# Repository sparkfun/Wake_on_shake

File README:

Design files for the Wake-on-shake board.

Firmware compiled in WinAVR-20100110.
EAGLE development in 6.3.0.

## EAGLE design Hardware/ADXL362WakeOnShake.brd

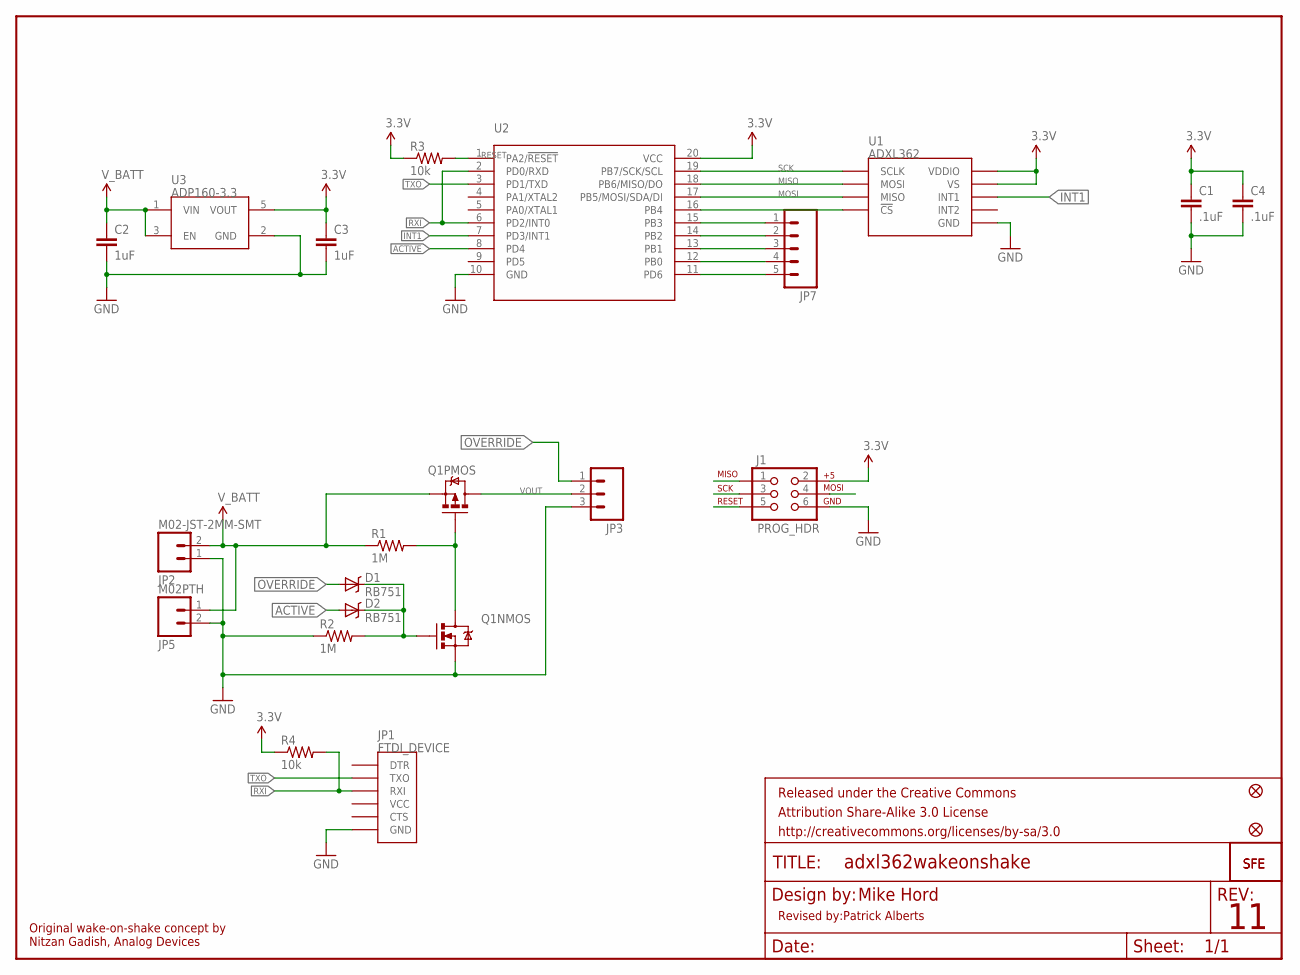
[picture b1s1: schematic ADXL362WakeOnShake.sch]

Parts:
C1, C4: .1uF; 0603-CAP
C2, C3: 1uF; 0603-CAP
D1, D2: RB751; SOD-523
FID1, FID2: FIDUCIAL1X2; FIDUCIAL-1X2
FRAME1: FRAME-LETTER; CREATIVE_COMMONS
J1: PROG_HDR; 2X3
JP1: FTDI_DEVICE; FTDI_DEVICE_SIDE
JP2: M02-JST-2MM-SMT; JST-2-SMD
JP3: M03PTH; 1X03
JP4: LOGO-SFENW2; SFE-NEW-WEB
JP5: M02PTH; 1X02
JP6: LOGO-SFENEW; SFE-NEW-WEBLOGO
JP7: M05PTH; 1X05
Q1: IRF7509; MSOP8
R1, R2: 1M; 0603-RES
R3, R4: 10k; 0603-RES
U1: ADXL362; ADXL362-1:1
U2: ATTINY2313A; SOP20W
U3: ADP160-3.3; SOT23-5

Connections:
3.3V: C1.1, C3.1, C4.1, J1.2, R3.1, R4.1, U1.P$1 (VDDIO), U1.P$14 (VS), U2.20 (VCC), U3.5 (VOUT)
ACTIVE: D2.A, U2.8 (PD4)
GND: C1.2, C2.2, C3.2, C4.2, J1.6, JP1.P$6 (GND), JP2.1 (2), JP3.3, JP5.2, Q1.1 (S), R2.1, U1.P$12 (GND), U1.P$13 (GND), U1.P$16 (GND), U2.10 (GND), U3.2 (GND)
INT1: U1.P$11 (INT1), U2.7 (PD3/INT1)
MISO: J1.1, U1.P$6 (MOSI), U2.18 (PB6/MISO/DO)
MOSI: J1.4, U1.P$7 (MISO), U2.17 (PB5/MOSI/SDA/DI)
unnamed: Q1.4 (G), Q1.7 (D), Q1.8 (D), R1.2
unnamed: D1.C, D2.C, Q1.2 (G), R2.2
unnamed: JP7.1, U2.15 (PB3)
unnamed: JP7.2, U2.14 (PB2)
unnamed: JP7.3, U2.13 (PB1)
unnamed: JP7.4, U2.12 (PB0)
unnamed: U1.P$8 (!CS), U2.16 (PB4)
unnamed: JP7.5, U2.11 (PD6)
OVERRIDE: D1.A, JP3.1
RESET: J1.5, R3.2, U2.1 (PA2/!RESET)
RXI: JP1.P$3 (RXI), R4.2, U2.2 (PD0/RXD), U2.6 (PD2/INT0)
SCK: J1.3, U1.P$4 (SCLK), U2.19 (PB7/SCK/SCL)
TXO: JP1.P$2 (TXO), U2.3 (PD1/TXD)
VOUT: JP3.2, Q1.5 (D), Q1.6 (D)
V_BATT: C2.1, JP2.2 (1), JP5.1, Q1.3 (S), R1.1, U3.1 (VIN), U3.3 (EN)

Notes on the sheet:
Mike Hord
Original wake-on-shake concept by Nitzan Gadish, Analog Devices
Revised by:Patrick Alberts

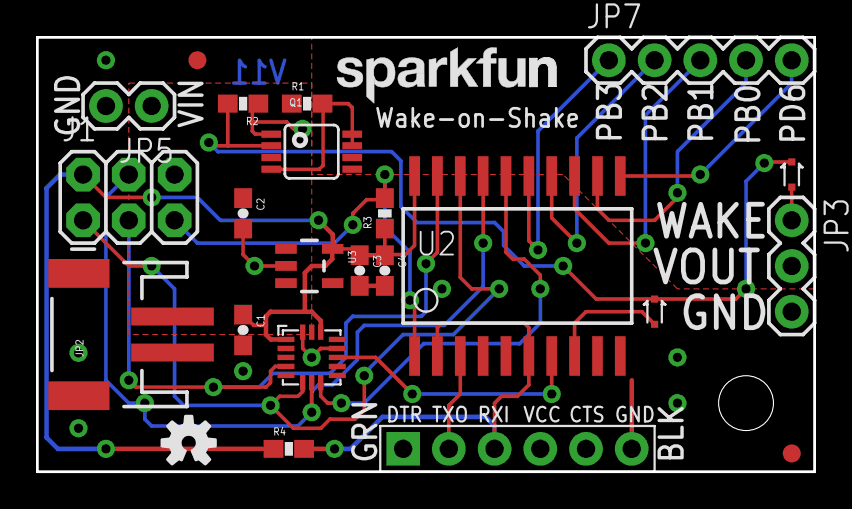
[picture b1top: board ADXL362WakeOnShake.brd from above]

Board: 2 copper layers, 43.2 x 24.1 mm, 27 parts (1 on the bottom side), 21 nets.

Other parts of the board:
U$3: OSHW-LOGO-S
U$4: STAND-OFF-TIGHT

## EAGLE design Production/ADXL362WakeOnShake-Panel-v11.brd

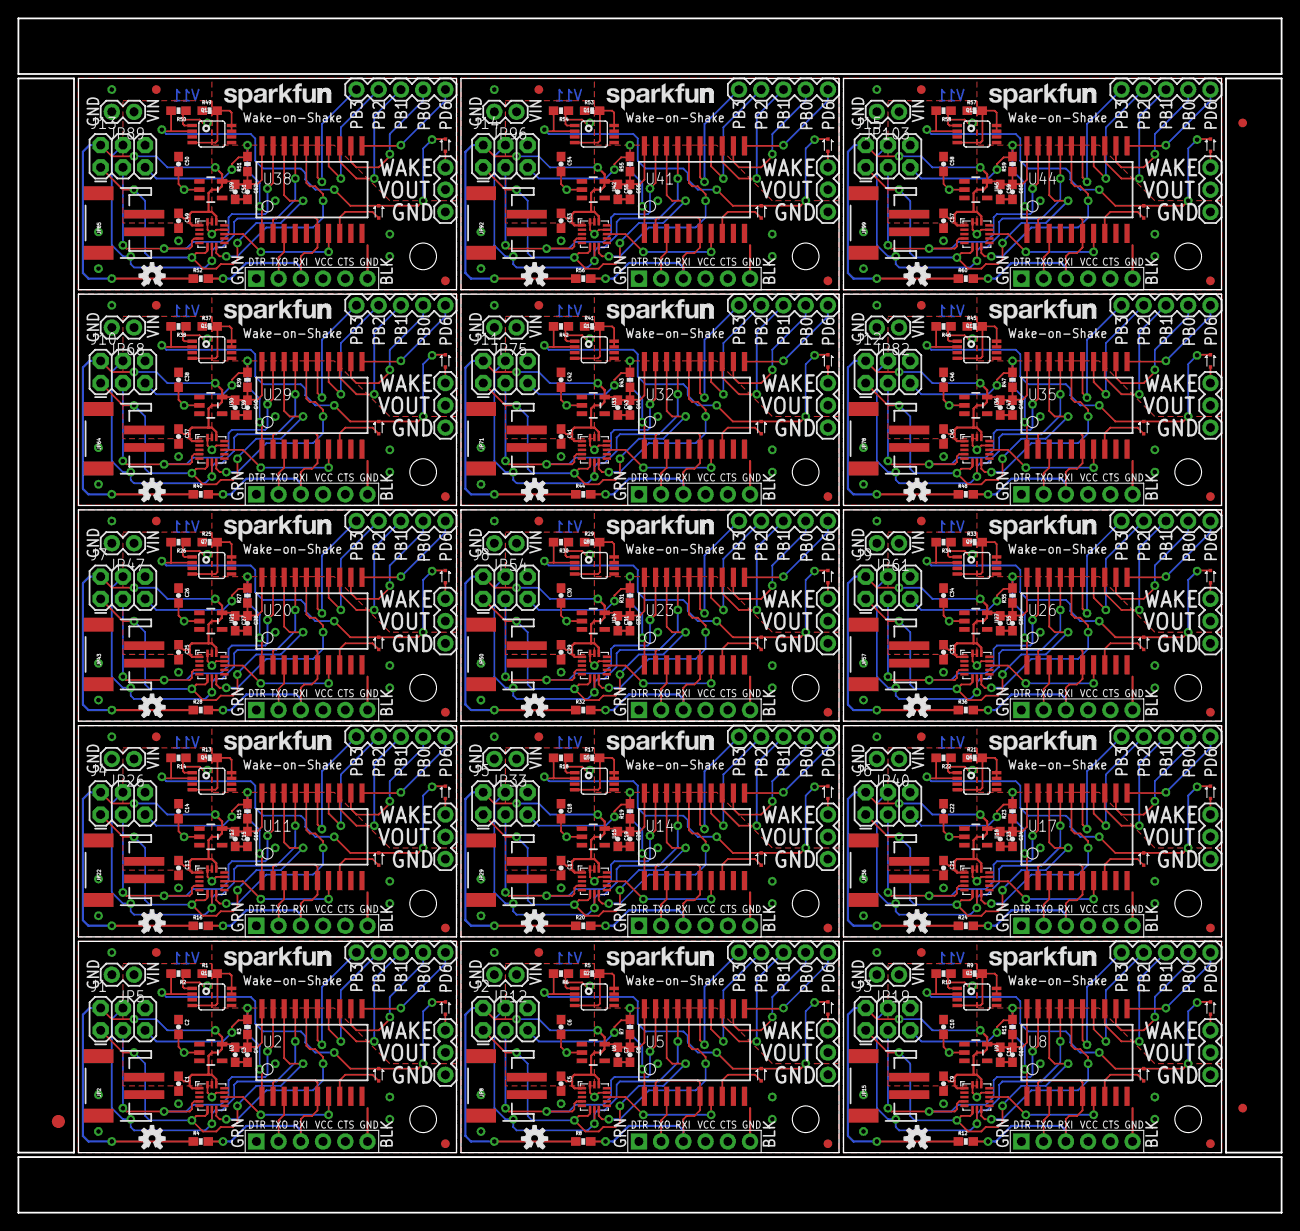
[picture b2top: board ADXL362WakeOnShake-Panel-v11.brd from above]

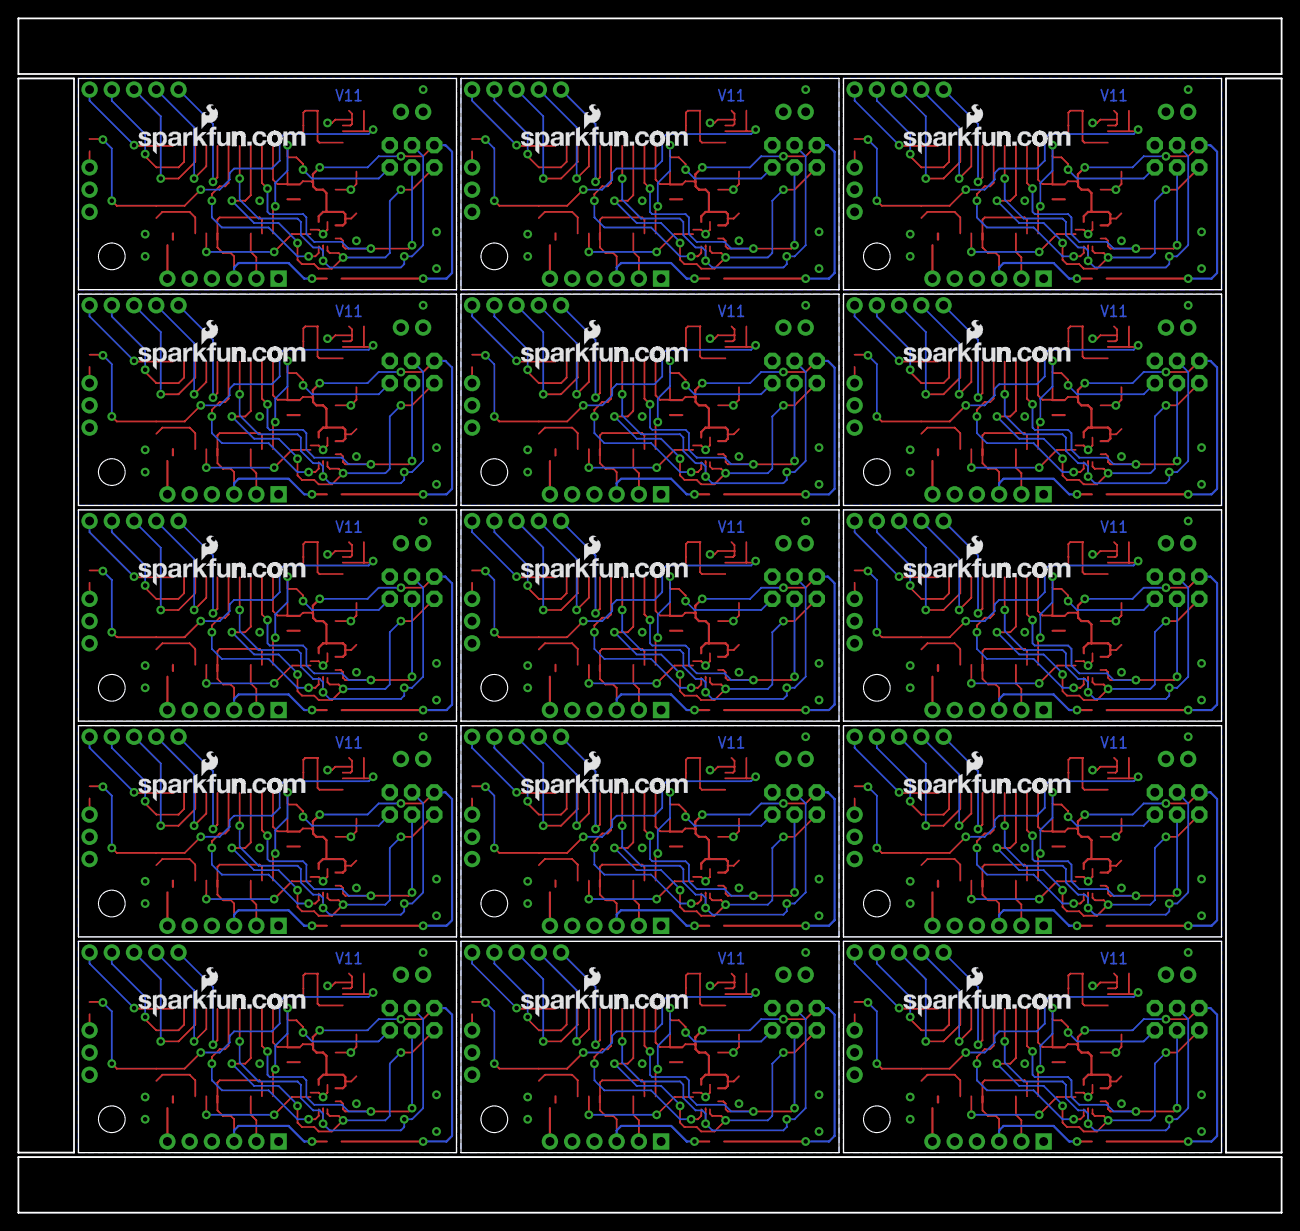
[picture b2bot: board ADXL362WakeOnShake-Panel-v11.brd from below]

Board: 2 copper layers, 144.3 x 136.4 mm, 393 parts (15 on the bottom side), 315 nets.

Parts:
C1, C4, C5, C8, C9, C12, C13, C16, C17, C20, C21, C24, C25, C28, C29, C32, C33, C36, C37, C40, C41, C44, C45, C48, C49, C52, C53, C56, C57, C60: .1uF; 0603-CAP
C2, C3, C6, C7, C10, C11, C14, C15, C18, C19, C22, C23, C26, C27, C30, C31, C34, C35, C38, C39, C42, C43, C46, C47, C50, C51, C54, C55, C58, C59: 1uF; 0603-CAP
D1, D2, D3, D4, D5, D6, D7, D8, D9, D10, D11, D12, D13, D14, D15, D16, D17, D18, D19, D20, D21, D22, D23, D24, D25, D26, D27, D28, D29, D30: RB751; SOD-523
E$1: FIDUCIAL-1.5X3
E$4, E$5: FIDUCIAL-1X2
FID1, FID2, FID3, FID4, FID5, FID6, FID7, FID8, FID9, FID10, FID11, FID12, FID13, FID14, FID15, FID16, FID17, FID18, FID19, FID20, FID21, FID22, FID23, FID24, FID25, FID26, FID27, FID28, FID29, FID30: FIDUCIAL1X2; FIDUCIAL-1X2
J1, J2, J3, J4, J5, J6, J7, J8, J9, J10, J11, J12, J13, J14, J15: PROG_HDR; 2X3
JP1, JP10, JP17, JP24, JP31, JP38, JP45, JP52, JP59, JP66, JP73, JP80, JP87, JP94, JP101: FTDI_DEVICE; FTDI_DEVICE_SIDE
JP2, JP8, JP15, JP22, JP29, JP36, JP43, JP50, JP57, JP64, JP71, JP78, JP85, JP92, JP99: M02-JST-2MM-SMT; JST-2-SMD
JP3, JP9, JP16, JP23, JP30, JP37, JP44, JP51, JP58, JP65, JP72, JP79, JP86, JP93, JP100: 1X03
JP4, JP11, JP18, JP25, JP32, JP39, JP46, JP53, JP60, JP67, JP74, JP81, JP88, JP95, JP102: LOGO-SFENW2; SFE-NEW-WEB
JP5, JP12, JP19, JP26, JP33, JP40, JP47, JP54, JP61, JP68, JP75, JP82, JP89, JP96, JP103: M02PTH; 1X02
JP6, JP13, JP20, JP27, JP34, JP41, JP48, JP55, JP62, JP69, JP76, JP83, JP90, JP97, JP104: LOGO-SFENEW; SFE-NEW-WEBLOGO
JP7, JP14, JP21, JP28, JP35, JP42, JP49, JP56, JP63, JP70, JP77, JP84, JP91, JP98, JP105: 1X05
Q1, Q2, Q3, Q4, Q5, Q6, Q7, Q8, Q9, Q10, Q11, Q12, Q13, Q14, Q15: MSOP8
R1, R2, R5, R6, R9, R10, R13, R14, R17, R18, R21, R22, R25, R26, R29, R30, R33, R34, R37, R38, R41, R42, R45, R46, R49, R50, R53, R54, R57, R58: 1M; 0603-RES
R3, R4, R7, R8, R11, R12, R15, R16, R19, R20, R23, R24, R27, R28, R31, R32, R35, R36, R39, R40, R43, R44, R47, R48, R51, R52, R55, R56, R59, R60: 10k; 0603-RES
U1, U4, U7, U10, U13, U16, U19, U22, U25, U28, U31, U34, U37, U40, U43: ADXL362; ADXL362-1:1
U2, U5, U8, U11, U14, U17, U20, U23, U26, U29, U32, U35, U38, U41, U44: SOP20W
U3, U6, U9, U12, U15, U18, U21, U24, U27, U30, U33, U36, U39, U42, U45: ADP160-3.3; SOT23-5
U$1, U$4, U$5, U$7, U$9, U$11, U$13, U$15, U$17, U$19, U$21, U$23, U$25, U$27, U$29: STAND-OFF-TIGHT
U$2, U$3, U$6, U$8, U$10, U$12, U$14, U$16, U$18, U$20, U$22, U$24, U$26, U$28, U$30: OSHW-LOGO-S

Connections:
3.3V: C1.1, C3.1, C4.1, J1.2, R3.1, R4.1, U1.P$1, U1.P$14, U2.20, U3.5
3.3V1: C5.1, C7.1, C8.1, J2.2, R7.1, R8.1, U4.P$1, U4.P$14, U5.20, U6.5
3.3V2: C9.1, C11.1, C12.1, J3.2, R11.1, R12.1, U7.P$1, U7.P$14, U8.20, U9.5
3.3V3: C13.1, C15.1, C16.1, J4.2, R15.1, R16.1, U10.P$1, U10.P$14, U11.20, U12.5
3.3V4: C17.1, C19.1, C20.1, J5.2, R19.1, R20.1, U13.P$1, U13.P$14, U14.20, U15.5
3.3V5: C21.1, C23.1, C24.1, J6.2, R23.1, R24.1, U16.P$1, U16.P$14, U17.20, U18.5
3.3V6: C25.1, C27.1, C28.1, J7.2, R27.1, R28.1, U19.P$1, U19.P$14, U20.20, U21.5
3.3V7: C29.1, C31.1, C32.1, J8.2, R31.1, R32.1, U22.P$1, U22.P$14, U23.20, U24.5
3.3V8: C33.1, C35.1, C36.1, J9.2, R35.1, R36.1, U25.P$1, U25.P$14, U26.20, U27.5
3.3V9: C37.1, C39.1, C40.1, J10.2, R39.1, R40.1, U28.P$1, U28.P$14, U29.20, U30.5
3.3V10: C41.1, C43.1, C44.1, J11.2, R43.1, R44.1, U31.P$1, U31.P$14, U32.20, U33.5
3.3V11: C45.1, C47.1, C48.1, J12.2, R47.1, R48.1, U34.P$1, U34.P$14, U35.20, U36.5
3.3V12: C49.1, C51.1, C52.1, J13.2, R51.1, R52.1, U37.P$1, U37.P$14, U38.20, U39.5
3.3V13: C53.1, C55.1, C56.1, J14.2, R55.1, R56.1, U40.P$1, U40.P$14, U41.20, U42.5
3.3V14: C57.1, C59.1, C60.1, J15.2, R59.1, R60.1, U43.P$1, U43.P$14, U44.20, U45.5
ACTIVE: D2.A, U2.8
ACTIVE1: D4.A, U5.8
ACTIVE2: D6.A, U8.8
ACTIVE3: D8.A, U11.8
ACTIVE4: D10.A, U14.8
ACTIVE5: D12.A, U17.8
ACTIVE6: D14.A, U20.8
ACTIVE7: D16.A, U23.8
ACTIVE8: D18.A, U26.8
ACTIVE9: D20.A, U29.8
ACTIVE10: D22.A, U32.8
ACTIVE11: D24.A, U35.8
ACTIVE12: D26.A, U38.8
ACTIVE13: D28.A, U41.8
ACTIVE14: D30.A, U44.8
GND: C1.2, C2.2, C3.2, C4.2, J1.6, JP1.P$6, JP2.1, JP3.3, JP5.2, Q1.1, R2.1, U1.P$12, U1.P$13, U1.P$16, U2.10, U3.2
GND1: C5.2, C6.2, C7.2, C8.2, J2.6, JP8.1, JP9.3, JP10.P$6, JP12.2, Q2.1, R6.1, U4.P$12, U4.P$13, U4.P$16, U5.10, U6.2
GND2: C9.2, C10.2, C11.2, C12.2, J3.6, JP15.1, JP16.3, JP17.P$6, JP19.2, Q3.1, R10.1, U7.P$12, U7.P$13, U7.P$16, U8.10, U9.2
GND3: C13.2, C14.2, C15.2, C16.2, J4.6, JP22.1, JP23.3, JP24.P$6, JP26.2, Q4.1, R14.1, U10.P$12, U10.P$13, U10.P$16, U11.10, U12.2
GND4: C17.2, C18.2, C19.2, C20.2, J5.6, JP29.1, JP30.3, JP31.P$6, JP33.2, Q5.1, R18.1, U13.P$12, U13.P$13, U13.P$16, U14.10, U15.2
GND5: C21.2, C22.2, C23.2, C24.2, J6.6, JP36.1, JP37.3, JP38.P$6, JP40.2, Q6.1, R22.1, U16.P$12, U16.P$13, U16.P$16, U17.10, U18.2
GND6: C25.2, C26.2, C27.2, C28.2, J7.6, JP43.1, JP44.3, JP45.P$6, JP47.2, Q7.1, R26.1, U19.P$12, U19.P$13, U19.P$16, U20.10, U21.2
GND7: C29.2, C30.2, C31.2, C32.2, J8.6, JP50.1, JP51.3, JP52.P$6, JP54.2, Q8.1, R30.1, U22.P$12, U22.P$13, U22.P$16, U23.10, U24.2
GND8: C33.2, C34.2, C35.2, C36.2, J9.6, JP57.1, JP58.3, JP59.P$6, JP61.2, Q9.1, R34.1, U25.P$12, U25.P$13, U25.P$16, U26.10, U27.2
GND9: C37.2, C38.2, C39.2, C40.2, J10.6, JP64.1, JP65.3, JP66.P$6, JP68.2, Q10.1, R38.1, U28.P$12, U28.P$13, U28.P$16, U29.10, U30.2
GND10: C41.2, C42.2, C43.2, C44.2, J11.6, JP71.1, JP72.3, JP73.P$6, JP75.2, Q11.1, R42.1, U31.P$12, U31.P$13, U31.P$16, U32.10, U33.2
GND11: C45.2, C46.2, C47.2, C48.2, J12.6, JP78.1, JP79.3, JP80.P$6, JP82.2, Q12.1, R46.1, U34.P$12, U34.P$13, U34.P$16, U35.10, U36.2
GND12: C49.2, C50.2, C51.2, C52.2, J13.6, JP85.1, JP86.3, JP87.P$6, JP89.2, Q13.1, R50.1, U37.P$12, U37.P$13, U37.P$16, U38.10, U39.2
GND13: C53.2, C54.2, C55.2, C56.2, J14.6, JP92.1, JP93.3, JP94.P$6, JP96.2, Q14.1, R54.1, U40.P$12, U40.P$13, U40.P$16, U41.10, U42.2
GND14: C57.2, C58.2, C59.2, C60.2, J15.6, JP99.1, JP100.3, JP101.P$6, JP103.2, Q15.1, R58.1, U43.P$12, U43.P$13, U43.P$16, U44.10, U45.2
INT1: U1.P$11, U2.7
INT2: U4.P$11, U5.7
INT3: U7.P$11, U8.7
INT4: U10.P$11, U11.7
INT5: U13.P$11, U14.7
INT6: U16.P$11, U17.7
INT7: U19.P$11, U20.7
INT8: U22.P$11, U23.7
INT9: U25.P$11, U26.7
INT10: U28.P$11, U29.7
INT11: U31.P$11, U32.7
INT12: U34.P$11, U35.7
INT13: U37.P$11, U38.7
INT14: U40.P$11, U41.7
INT15: U43.P$11, U44.7
MISO: J1.1, U1.P$6, U2.18
MISO1: J2.1, U4.P$6, U5.18
MISO2: J3.1, U7.P$6, U8.18
MISO3: J4.1, U10.P$6, U11.18
MISO4: J5.1, U13.P$6, U14.18
MISO5: J6.1, U16.P$6, U17.18
MISO6: J7.1, U19.P$6, U20.18
MISO7: J8.1, U22.P$6, U23.18
MISO8: J9.1, U25.P$6, U26.18
MISO9: J10.1, U28.P$6, U29.18
MISO10: J11.1, U31.P$6, U32.18
MISO11: J12.1, U34.P$6, U35.18
MISO12: J13.1, U37.P$6, U38.18
MISO13: J14.1, U40.P$6, U41.18
MISO14: J15.1, U43.P$6, U44.18
MOSI: J1.4, U1.P$7, U2.17
MOSI1: J2.4, U4.P$7, U5.17
MOSI2: J3.4, U7.P$7, U8.17
MOSI3: J4.4, U10.P$7, U11.17
MOSI4: J5.4, U13.P$7, U14.17
MOSI5: J6.4, U16.P$7, U17.17
MOSI6: J7.4, U19.P$7, U20.17
MOSI7: J8.4, U22.P$7, U23.17
MOSI8: J9.4, U25.P$7, U26.17
MOSI9: J10.4, U28.P$7, U29.17
MOSI10: J11.4, U31.P$7, U32.17
MOSI11: J12.4, U34.P$7, U35.17
MOSI12: J13.4, U37.P$7, U38.17
MOSI13: J14.4, U40.P$7, U41.17
MOSI14: J15.4, U43.P$7, U44.17
unnamed: Q1.4, Q1.7, Q1.8, R1.2
unnamed: D1.C, D2.C, Q1.2, R2.2
unnamed: JP7.1, U2.15
unnamed: JP7.2, U2.14
unnamed: JP7.3, U2.13
unnamed: JP7.4, U2.12
unnamed: U1.P$8, U2.16
unnamed: JP7.5, U2.11
unnamed: Q2.4, Q2.7, Q2.8, R5.2
unnamed: D3.C, D4.C, Q2.2, R6.2
unnamed: U4.P$8, U5.16
unnamed: JP14.1, U5.15
unnamed: JP14.2, U5.14
unnamed: JP14.3, U5.13
unnamed: JP14.4, U5.12
unnamed: JP14.5, U5.11
unnamed: Q3.4, Q3.7, Q3.8, R9.2
unnamed: D5.C, D6.C, Q3.2, R10.2
unnamed: U7.P$8, U8.16
unnamed: JP21.1, U8.15
unnamed: JP21.2, U8.14
unnamed: JP21.3, U8.13
unnamed: JP21.4, U8.12
unnamed: JP21.5, U8.11
unnamed: Q4.4, Q4.7, Q4.8, R13.2
unnamed: D7.C, D8.C, Q4.2, R14.2
unnamed: U10.P$8, U11.16
unnamed: JP28.1, U11.15
unnamed: JP28.2, U11.14
unnamed: JP28.3, U11.13
unnamed: JP28.4, U11.12
unnamed: JP28.5, U11.11
unnamed: Q5.4, Q5.7, Q5.8, R17.2
unnamed: D9.C, D10.C, Q5.2, R18.2
unnamed: U13.P$8, U14.16
unnamed: JP35.1, U14.15
unnamed: JP35.2, U14.14
unnamed: JP35.3, U14.13
unnamed: JP35.4, U14.12
unnamed: JP35.5, U14.11
unnamed: Q6.4, Q6.7, Q6.8, R21.2
unnamed: D11.C, D12.C, Q6.2, R22.2
unnamed: U16.P$8, U17.16
unnamed: JP42.1, U17.15
unnamed: JP42.2, U17.14
unnamed: JP42.3, U17.13
unnamed: JP42.4, U17.12
unnamed: JP42.5, U17.11
unnamed: Q7.4, Q7.7, Q7.8, R25.2
unnamed: D13.C, D14.C, Q7.2, R26.2
unnamed: U19.P$8, U20.16
unnamed: JP49.1, U20.15
unnamed: JP49.2, U20.14
unnamed: JP49.3, U20.13
unnamed: JP49.4, U20.12
unnamed: JP49.5, U20.11
unnamed: Q8.4, Q8.7, Q8.8, R29.2
unnamed: D15.C, D16.C, Q8.2, R30.2
unnamed: U22.P$8, U23.16
unnamed: JP56.1, U23.15
unnamed: JP56.2, U23.14
unnamed: JP56.3, U23.13
unnamed: JP56.4, U23.12
unnamed: JP56.5, U23.11
unnamed: Q9.4, Q9.7, Q9.8, R33.2
unnamed: D17.C, D18.C, Q9.2, R34.2
unnamed: U25.P$8, U26.16
unnamed: JP63.1, U26.15
unnamed: JP63.2, U26.14
unnamed: JP63.3, U26.13
unnamed: JP63.4, U26.12
unnamed: JP63.5, U26.11
unnamed: Q10.4, Q10.7, Q10.8, R37.2
unnamed: D19.C, D20.C, Q10.2, R38.2
unnamed: U28.P$8, U29.16
unnamed: JP70.1, U29.15
unnamed: JP70.2, U29.14
unnamed: JP70.3, U29.13
unnamed: JP70.4, U29.12
unnamed: JP70.5, U29.11
unnamed: Q11.4, Q11.7, Q11.8, R41.2
unnamed: D21.C, D22.C, Q11.2, R42.2
unnamed: U31.P$8, U32.16
unnamed: JP77.1, U32.15
unnamed: JP77.2, U32.14
unnamed: JP77.3, U32.13
unnamed: JP77.4, U32.12
unnamed: JP77.5, U32.11
unnamed: Q12.4, Q12.7, Q12.8, R45.2
unnamed: D23.C, D24.C, Q12.2, R46.2
unnamed: U34.P$8, U35.16
unnamed: JP84.1, U35.15
unnamed: JP84.2, U35.14
unnamed: JP84.3, U35.13
unnamed: JP84.4, U35.12
unnamed: JP84.5, U35.11
unnamed: Q13.4, Q13.7, Q13.8, R49.2
unnamed: D25.C, D26.C, Q13.2, R50.2
unnamed: U37.P$8, U38.16
unnamed: JP91.1, U38.15
unnamed: JP91.2, U38.14
unnamed: JP91.3, U38.13
unnamed: JP91.4, U38.12
unnamed: JP91.5, U38.11
unnamed: Q14.4, Q14.7, Q14.8, R53.2
unnamed: D27.C, D28.C, Q14.2, R54.2
unnamed: U40.P$8, U41.16
unnamed: JP98.1, U41.15
unnamed: JP98.2, U41.14
unnamed: JP98.3, U41.13
unnamed: JP98.4, U41.12
unnamed: JP98.5, U41.11
unnamed: Q15.4, Q15.7, Q15.8, R57.2
unnamed: D29.C, D30.C, Q15.2, R58.2
unnamed: U43.P$8, U44.16
unnamed: JP105.1, U44.15
unnamed: JP105.2, U44.14
unnamed: JP105.3, U44.13
unnamed: JP105.4, U44.12
unnamed: JP105.5, U44.11
OVERRIDE: D1.A, JP3.1
OVERRIDE1: D3.A, JP9.1
OVERRIDE2: D5.A, JP16.1
OVERRIDE3: D7.A, JP23.1
OVERRIDE4: D9.A, JP30.1
OVERRIDE5: D11.A, JP37.1
OVERRIDE6: D13.A, JP44.1
OVERRIDE7: D15.A, JP51.1
OVERRIDE8: D17.A, JP58.1
OVERRIDE9: D19.A, JP65.1
OVERRIDE10: D21.A, JP72.1
OVERRIDE11: D23.A, JP79.1
OVERRIDE12: D25.A, JP86.1
OVERRIDE13: D27.A, JP93.1
OVERRIDE14: D29.A, JP100.1
RESET: J1.5, R3.2, U2.1
RESET1: J2.5, R7.2, U5.1
RESET2: J3.5, R11.2, U8.1
RESET3: J4.5, R15.2, U11.1
RESET4: J5.5, R19.2, U14.1
RESET5: J6.5, R23.2, U17.1
RESET6: J7.5, R27.2, U20.1
RESET7: J8.5, R31.2, U23.1
RESET8: J9.5, R35.2, U26.1
RESET9: J10.5, R39.2, U29.1
RESET10: J11.5, R43.2, U32.1
RESET11: J12.5, R47.2, U35.1
RESET12: J13.5, R51.2, U38.1
RESET13: J14.5, R55.2, U41.1
RESET14: J15.5, R59.2, U44.1
RXI: JP1.P$3, R4.2, U2.2, U2.6
RXI1: JP10.P$3, R8.2, U5.2, U5.6
RXI2: JP17.P$3, R12.2, U8.2, U8.6
RXI3: JP24.P$3, R16.2, U11.2, U11.6
RXI4: JP31.P$3, R20.2, U14.2, U14.6
RXI5: JP38.P$3, R24.2, U17.2, U17.6
RXI6: JP45.P$3, R28.2, U20.2, U20.6
RXI7: JP52.P$3, R32.2, U23.2, U23.6
RXI8: JP59.P$3, R36.2, U26.2, U26.6
RXI9: JP66.P$3, R40.2, U29.2, U29.6
RXI10: JP73.P$3, R44.2, U32.2, U32.6
RXI11: JP80.P$3, R48.2, U35.2, U35.6
RXI12: JP87.P$3, R52.2, U38.2, U38.6
RXI13: JP94.P$3, R56.2, U41.2, U41.6
RXI14: JP101.P$3, R60.2, U44.2, U44.6
SCK: J1.3, U1.P$4, U2.19
SCK1: J2.3, U4.P$4, U5.19
SCK2: J3.3, U7.P$4, U8.19
SCK3: J4.3, U10.P$4, U11.19
SCK4: J5.3, U13.P$4, U14.19
SCK5: J6.3, U16.P$4, U17.19
SCK6: J7.3, U19.P$4, U20.19
SCK7: J8.3, U22.P$4, U23.19
SCK8: J9.3, U25.P$4, U26.19
SCK9: J10.3, U28.P$4, U29.19
SCK10: J11.3, U31.P$4, U32.19
SCK11: J12.3, U34.P$4, U35.19
SCK12: J13.3, U37.P$4, U38.19
SCK13: J14.3, U40.P$4, U41.19
SCK14: J15.3, U43.P$4, U44.19
TXO: JP1.P$2, U2.3
TXO1: JP10.P$2, U5.3
TXO2: JP17.P$2, U8.3
TXO3: JP24.P$2, U11.3
TXO4: JP31.P$2, U14.3
TXO5: JP38.P$2, U17.3
TXO6: JP45.P$2, U20.3
TXO7: JP52.P$2, U23.3
TXO8: JP59.P$2, U26.3
TXO9: JP66.P$2, U29.3
TXO10: JP73.P$2, U32.3
TXO11: JP80.P$2, U35.3
TXO12: JP87.P$2, U38.3
TXO13: JP94.P$2, U41.3
TXO14: JP101.P$2, U44.3
VOUT: JP3.2, Q1.5, Q1.6
VOUT1: JP9.2, Q2.5, Q2.6
VOUT2: JP16.2, Q3.5, Q3.6
VOUT3: JP23.2, Q4.5, Q4.6
VOUT4: JP30.2, Q5.5, Q5.6
VOUT5: JP37.2, Q6.5, Q6.6
VOUT6: JP44.2, Q7.5, Q7.6
VOUT7: JP51.2, Q8.5, Q8.6
VOUT8: JP58.2, Q9.5, Q9.6
VOUT9: JP65.2, Q10.5, Q10.6
VOUT10: JP72.2, Q11.5, Q11.6
VOUT11: JP79.2, Q12.5, Q12.6
VOUT12: JP86.2, Q13.5, Q13.6
VOUT13: JP93.2, Q14.5, Q14.6
VOUT14: JP100.2, Q15.5, Q15.6
V_BATT: C2.1, JP2.2, JP5.1, Q1.3, R1.1, U3.1, U3.3
V_BATT1: C6.1, JP8.2, JP12.1, Q2.3, R5.1, U6.1, U6.3
V_BATT2: C10.1, JP15.2, JP19.1, Q3.3, R9.1, U9.1, U9.3
V_BATT3: C14.1, JP22.2, JP26.1, Q4.3, R13.1, U12.1, U12.3
V_BATT4: C18.1, JP29.2, JP33.1, Q5.3, R17.1, U15.1, U15.3
V_BATT5: C22.1, JP36.2, JP40.1, Q6.3, R21.1, U18.1, U18.3
V_BATT6: C26.1, JP43.2, JP47.1, Q7.3, R25.1, U21.1, U21.3
V_BATT7: C30.1, JP50.2, JP54.1, Q8.3, R29.1, U24.1, U24.3
V_BATT8: C34.1, JP57.2, JP61.1, Q9.3, R33.1, U27.1, U27.3
V_BATT9: C38.1, JP64.2, JP68.1, Q10.3, R37.1, U30.1, U30.3
V_BATT10: C42.1, JP71.2, JP75.1, Q11.3, R41.1, U33.1, U33.3
V_BATT11: C46.1, JP78.2, JP82.1, Q12.3, R45.1, U36.1, U36.3
V_BATT12: C50.1, JP85.2, JP89.1, Q13.3, R49.1, U39.1, U39.3
V_BATT13: C54.1, JP92.2, JP96.1, Q14.3, R53.1, U42.1, U42.3
V_BATT14: C58.1, JP99.2, JP103.1, Q15.3, R57.1, U45.1, U45.3

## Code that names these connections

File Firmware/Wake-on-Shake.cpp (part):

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	// Port A- both pins are unused, so we'll make them both outputs and drive them
	//   low to save power.
	DDRA = (1<<PA1) | (1<<PA0);
	// Port B- PB0-3 are unused; make them outputs and tie them low. PB4 is !CS
	//   for the ADXL362, so it should be an output. PB5 is MISO from the ADXL362, so
	//   leave it an input. PB6 is MOSI to ADXL362, and PB7 is SCK, so they should be
	//   outputs.
	DDRB = (1<<PB7) | (1<<PB6) | (1<<PB4) | (1<<PB3) | (1<<PB2)| (1<<PB1) | (1<<PB0);
	// No port C pins on this chip
	// Port D- PD0 is the serial receive input. PD1 is serial transmit output. PD2 is
	//   is an external interrupt used to wake the processor on serial activity. PD3
	//   is the interrupt from the ADXL362, used to wake the device on detected
	//   motion. PD4 is the MOSFET turn-on signal, so should be an output. PD5 and
	//   PD6 are unused; make them outputs and tie them low. PD7 doesn't exist.
	DDRD = (1<<PD6) | (1<<PD5) | (1<<PD4) | (1<<PD1);
	
	// Now let's configure some initial IO states
	
	// Port A- both set low to reduce current consumption
	PORTA = (0<<PA1) | (0<<PA0);
	// Port B- PB0-3 should be low for power consumption; PB4 is !CS, so bring it
	//   high to keep the ADXL362 non-selected. Others are don't care.
	PORTB = (1<<PB4) | (0<<PB3) | (0<<PB2) | (0<<PB1) | (0<<PB0);
	// Port C doesn't exist
	// Port D- PD5 and PD6 should be tied low; others are (for now) don't care.
	//   Also, PD2/PD0 should be made high to enable pullup resistor for when no
	//   serial connection is present.
	PORTD = (1<<PD6) | (1<<PD5) | (1<<PD2) | (1<<PD0);
	
	// Interrupt configuration is next. We'll need two interrupts: INT0 and INT1.
	//   INT0 will wiggle when a serial connection occurs. INT1 will wiggle when
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
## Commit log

2012-10-10 Initial commit. Board v02, firmware not completed.
2012-11-15 Initial firmware commit (for non-Arduino based stuff).
    This is an AVRStudio6 project; right now, all the pieces are working (serial,
    EEPROM, SPI, interrupts, etc etc), but the bits aren't tied together very
    well. The UI doesn't really work all that well.
2012-11-15 Things playing more nicely, now. Readback from EEPROM produces wrong values; not sure if it's bad write or bad read or both.
    Interrupts greatly simplified; size of RX interrupt was causing either
    a non-reentrant code error or a stack overflow.
2012-11-16 Hasn't been tested yet, and needs some comments placed into the code.
    Core functionality is in place and it seems to be working okay, though.
2012-11-19 Updating hardware files to v10: - FTDI header silk changed to accurately reflect pin names - moved some traces to avoid silk/via collision - added 10k resistor pull-up on RX line - FTDI header was sl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
    Changes to Firmware are purely machine changes to project files.
2012-11-20 Tweaked the silk slightly so that there is a distinction between VIN and VOUT instead of them being both V+.
2012-11-20 Added part number info for the accelerometer and changed the version number on the bottom copper layer.
2012-11-20 Made loadOn and loadOff macros to save memory. Also moved delay length sanity check from read time to write time, so that advanced users can bypass it with the (not yet implemented) direct EEPROM wri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
2013-01-16 Deleted AVR Studio crap.
2013-01-16 Convert to C and to ANSI.
2013-01-17 Go back to the AVR Studio version
2013-01-17 Okay, I really made a dog's dinner of this.
    Apparently, the last *useful* commit was actually pretty incomplete.
    I managed to delete a few important files, revert some stuff, and
    generally just screw up my life. Fortunately, Windows (or maybe
    Dropbox?) was able to take me back to a version of the folder from
    last week, before I started on this ill-fated comedy of errors.
    This commit effectively removes the AVR studio junk and moves all
2013-01-17 Production release candidate.
    -Converted .cpp files to .c
    -Converted UTF-8 encoded files to ANSI
    -Added a newline command to serial to save size
    -Changed some print messages to reduce size
2013-01-17 Changed README, rm .hex from .gitignore
2013-01-17 Add .hex file to repo
2013-01-18 Minor updates - Fixed spelling errors in user guide. - Fixed minor issues in the ui.c
2013-01-22 Fixed some issues in the pin read/write functions in ui.c: - Write low was using logical NOT (!) instead of bitwise NOT (~) which was causing it to clear all pins instead of just one. - Read was usin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
2013-01-24 A few minor changes: - One of the function prototypes in ADXL362.h had a typo. - Increased the baud rate from 2400bps to 9600bps because the Arduino software serial library doesn't seem to like 2400b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
2013-02-13 Added PDF version of user's guide.
2013-02-15 Added attribution for original concept.
2013-03-07 porting readme to markdown and prettyfying. license info needed.
2013-05-18 Update User Guide 9600 baud and add graphics to ODT file to ease PDF regeneration
2013-05-28 Update Wake-on-Shake.c
    There were conflicting comments regarding baud rate. Made it consistent.
2014-02-12 Updated caps, res, sch, vers# and diodes
    Updated caps/res to 0603 , 1:1 on the adxl362, updated footprint for
    diodes, new rev #
2014-03-21 Fixed FDTI ann rings / added standoff
2014-04-17 added regular fiducials
2014-04-17 Created panel v11
2014-11-04 Updating README information for repository
2015-03-03 Uploading example code for new Learn tutorial
2015-03-03 Adding neopixel sketch demo
2015-03-03 Fixing README typo
2017-01-02 Fixing 'nix builds (Case-Sensitive)
2025-06-27 Update README.md
    Updating link

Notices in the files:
Firmware/Wake-on-Shake.cpp:
Wake-on-Shake hardware and firmware are released under the Creative Commons
Share Alike v3.0 license:
http://creativecommons.org/licenses/by-sa/3.0
parts and their libraries:
SparkFun-DiscreteSemi: Licensing: CC v3.0 Share-Alike You are welcome to use this library for commercial purposes.
SparkFun-Aesthetics: Released under the Creative Commons Attribution Share-Alike 3.0 License
SparkFun-Aesthetics: Released under the Creative Commons
